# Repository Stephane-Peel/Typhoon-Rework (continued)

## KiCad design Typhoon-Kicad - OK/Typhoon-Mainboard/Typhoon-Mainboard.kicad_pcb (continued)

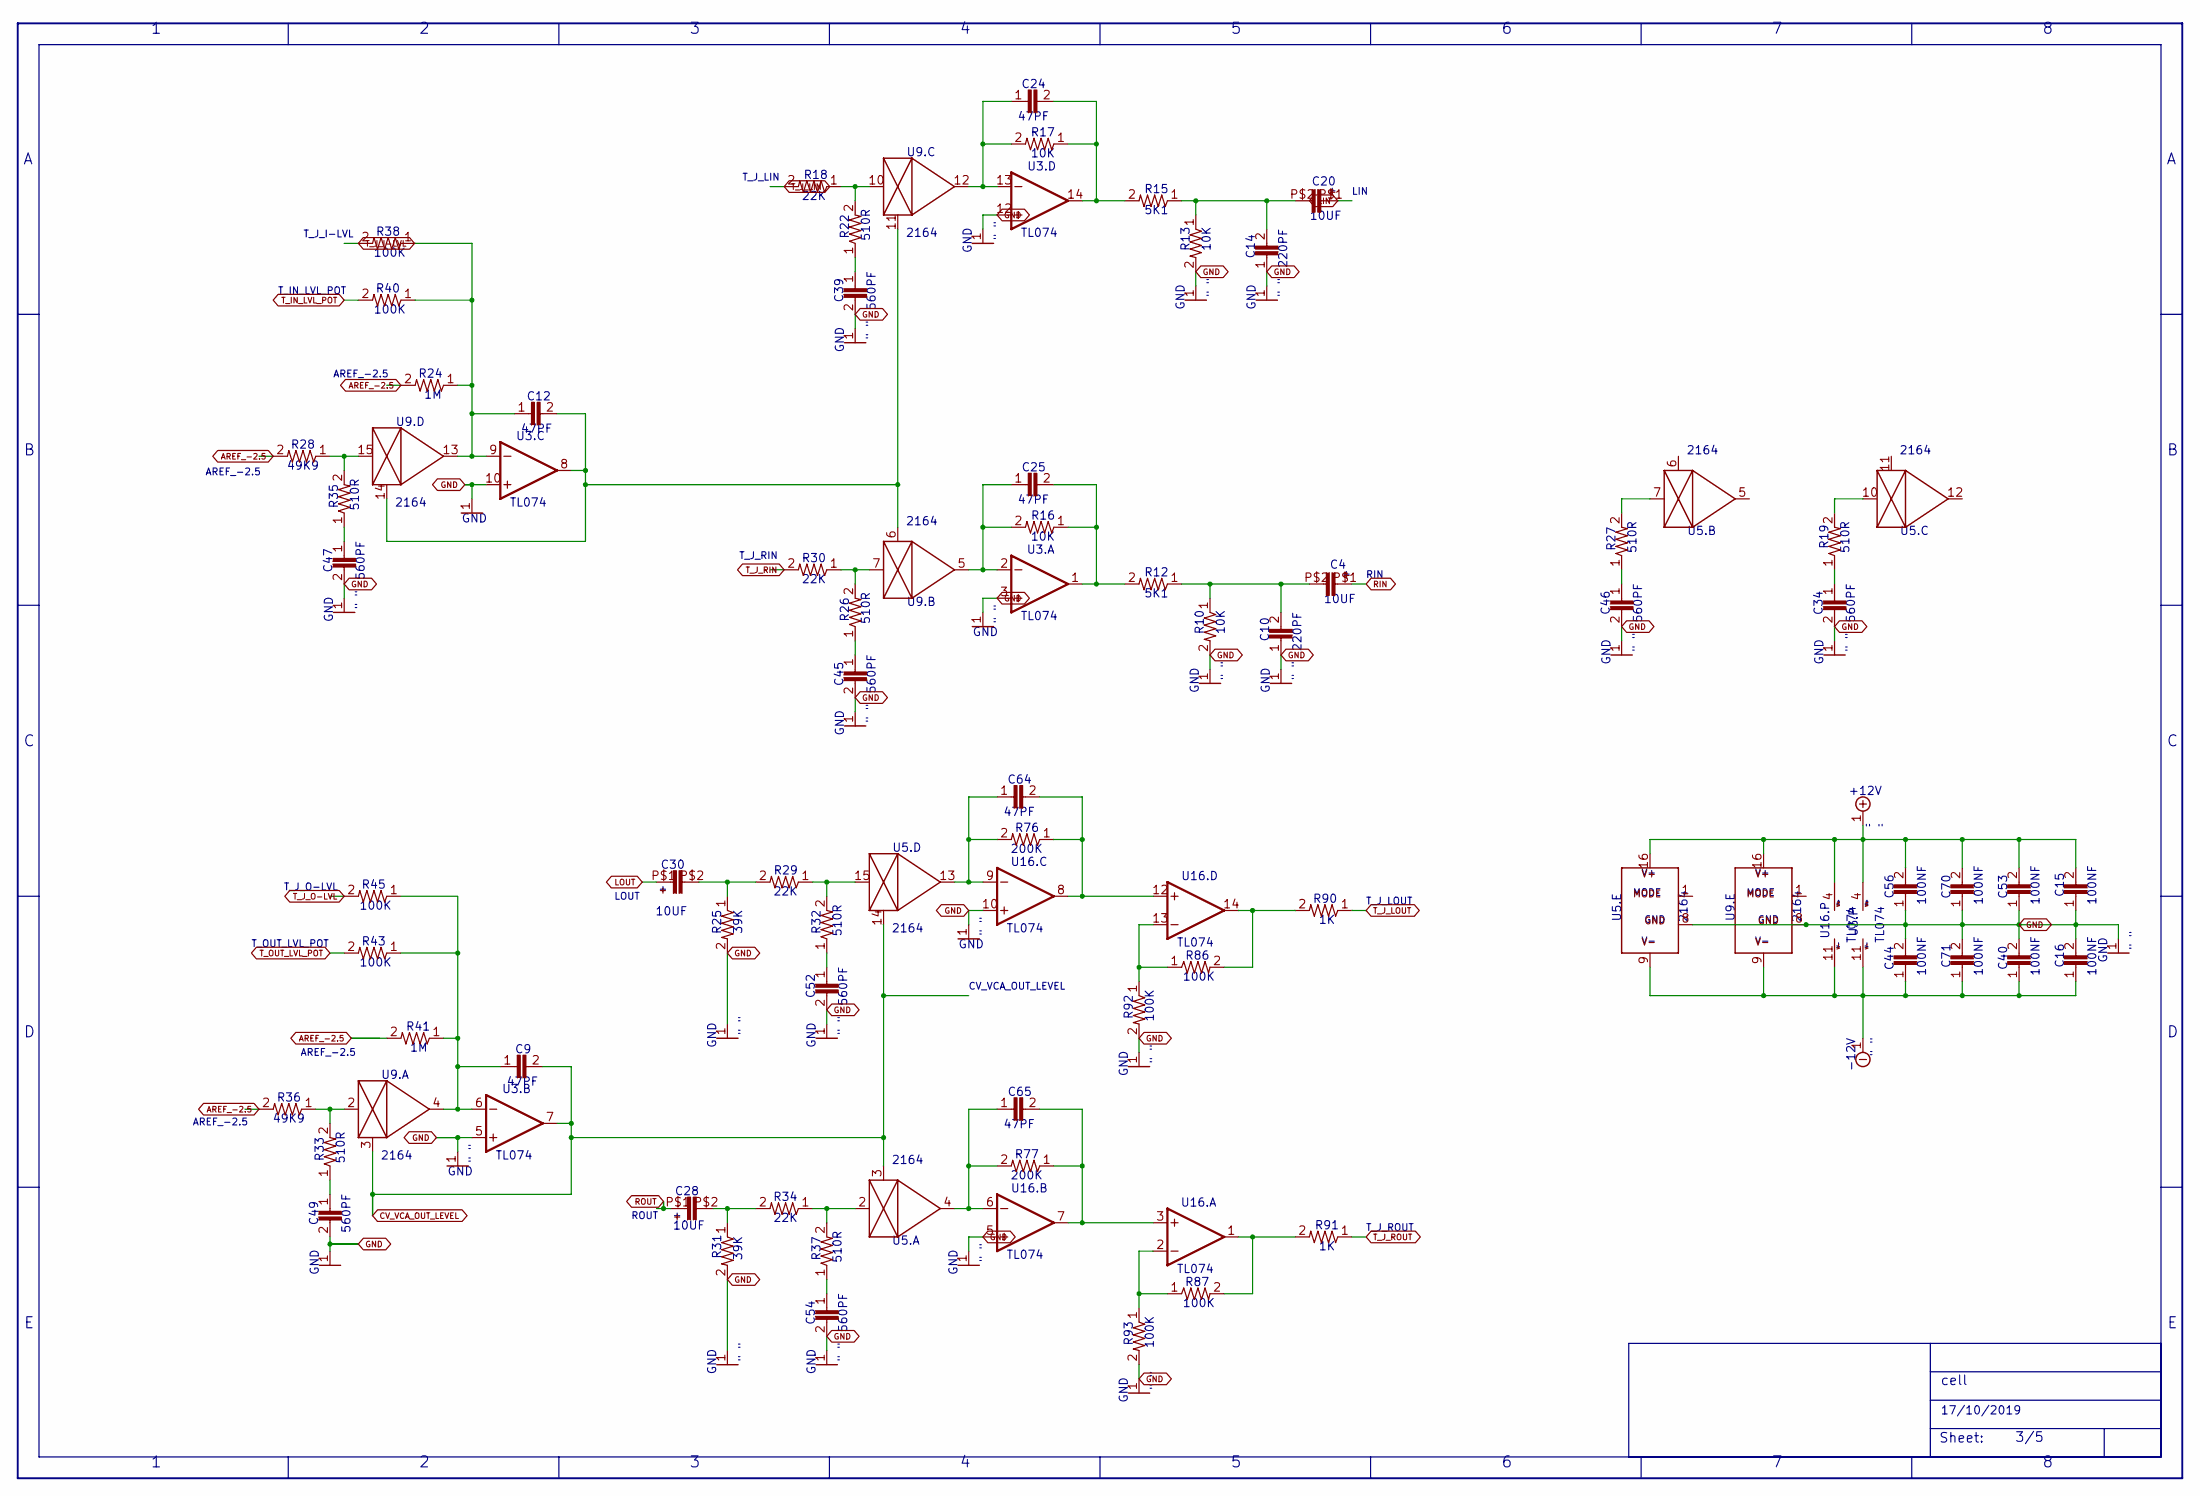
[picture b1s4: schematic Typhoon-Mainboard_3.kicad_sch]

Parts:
C4, C20, C28, C30: 10UF; EC-4X7
C9, C12, C24, C25, C64, C65: 47PF; CAP_0603
C10, C14: 220PF; CAP_0603
C15, C16, C40, C44, C53, C56, C70, C71: 100NF; CAP_0603
C34, C39, C45, C46, C47, C49, C52, C54: 560PF; CAP_0603
R10, R13, R16, R17: 10K; RES_0603
R12, R15: 5K1; RES_0603
R18, R29, R30, R34: 22K; RES_0603
R19, R22, R26, R27, R32, R33, R35, R37: 510R; RES_0603
R24, R41: 1M; RES_0603
R25, R31: 39K; RES_0603
R28, R36: 49K9; RES_0603
R38, R40, R43, R45, R86, R87, R92, R93: 100K; RES_0603
R76, R77: 200K; RES_0603
R90, R91: 1K; RES_0603
U3, U16: TL074; SO-14
U5, U9: 2164; SO-16

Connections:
+12V: C15.2, C53.2, C56.2, C70.2, U3.4 (V+), U5.16 (V+), U9.16 (V+), U16.4 (V+); also elsewhere on the board
-12V: C16.1, C40.1, C44.1, C71.1, U3.11 (V-), U5.9 (V-), U9.9 (V-), U16.11 (V-); also elsewhere on the board
AREF_-2.5: R24.2, R28.2, R36.2, R41.2; also elsewhere on the board
CV_VCA_OUT_LEVEL: C9.2, U3.7 (OUT), U5.3 (CTRL), U5.14 (CTRL), U9.3 (CTRL); also elsewhere on the board
LIN: C20.P$1 (POS); also elsewhere on the board
LOUT: C30.P$1 (POS); also elsewhere on the board
unnamed: C39.1, R22.1
unnamed: C45.1, R26.1
unnamed: C47.1, R35.1
unnamed: C12.2, U3.8 (OUT), U9.6 (CTRL), U9.11 (CTRL), U9.14 (CTRL)
unnamed: R26.2, R30.1, U9.7 (IN)
unnamed: R28.1, R35.2, U9.15 (IN)
unnamed: C25.1, R16.2, U3.2 (-IN), U9.5 (OUT)
unnamed: C25.2, R12.2, R16.1, U3.1 (OUT)
unnamed: C49.1, R33.1
unnamed: R33.2, R36.1, U9.2 (IN)
unnamed: C64.1, R76.2, U5.13 (OUT), U16.9 (-IN)
unnamed: C64.2, R76.1, U16.8 (OUT), U16.12 (+IN)
unnamed: R18.1, R22.2, U9.10 (IN)
unnamed: R27.2, U5.7 (IN)
unnamed: R29.1, R32.2, U5.15 (IN)
unnamed: C52.1, R32.1
unnamed: C30.P$2 (NEG), R25.1, R29.2
unnamed: C4.P$2 (NEG), C10.2, R10.1, R12.1
unnamed: C65.1, R77.2, U5.4 (OUT), U16.6 (-IN)
unnamed: C65.2, R77.1, U16.3 (+IN), U16.7 (OUT)
unnamed: R34.1, R37.2, U5.2 (IN)
unnamed: C54.1, R37.1
unnamed: C28.P$2 (NEG), R31.1, R34.2
unnamed: R19.2, U5.10 (IN)
unnamed: C24.1, R17.2, U3.13 (-IN), U9.12 (OUT)
unnamed: C24.2, R15.2, R17.1, U3.14 (OUT)
unnamed: R86.1, R92.1, U16.13 (-IN)
unnamed: C46.1, R27.1
unnamed: C34.1, R19.1
unnamed: R86.2, R90.2, U16.14 (OUT)
unnamed: R87.1, R93.1, U16.2 (-IN)
unnamed: R87.2, R91.2, U16.1 (OUT)
unnamed: C14.2, C20.P$2 (NEG), R13.1, R15.1
RIN: C4.P$1 (POS); also elsewhere on the board
ROUT: C28.P$1 (POS); also elsewhere on the board
T_IN_LVL_POT: R40.2; also elsewhere on the board
T_J_I-LVL: R38.2; also elsewhere on the board
T_J_LIN: R18.2; also elsewhere on the board
T_J_LOUT: R90.1; also elsewhere on the board
T_J_O-LVL: R45.2; also elsewhere on the board
T_J_RIN: R30.2; also elsewhere on the board
T_J_ROUT: R91.1; also elsewhere on the board
T_OUT_LVL_POT: R43.2; also elsewhere on the board
VCA_CTRL_INPUTS: C12.1, R24.1, R38.1, R40.1, U3.9 (-IN), U9.13 (OUT)
VCA_CTRL_INPUTS1: C9.1, R41.1, R43.1, R45.1, U3.6 (-IN), U9.4 (OUT)

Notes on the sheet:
TL074
C10
220PF
C64
R30
" "
R26
47PF
100NF
510R
C34
T_J_O-LVL
GND
22K
U9.D
560PF
C44
2164
R93
100K
T_J_ROUT
R24
10K
10UF
C70
U3.D
17/10/2019
R32
R91
C45
5K1
R90
RIN
MODE
R17
C53
U9.A
49K9
200K
C65

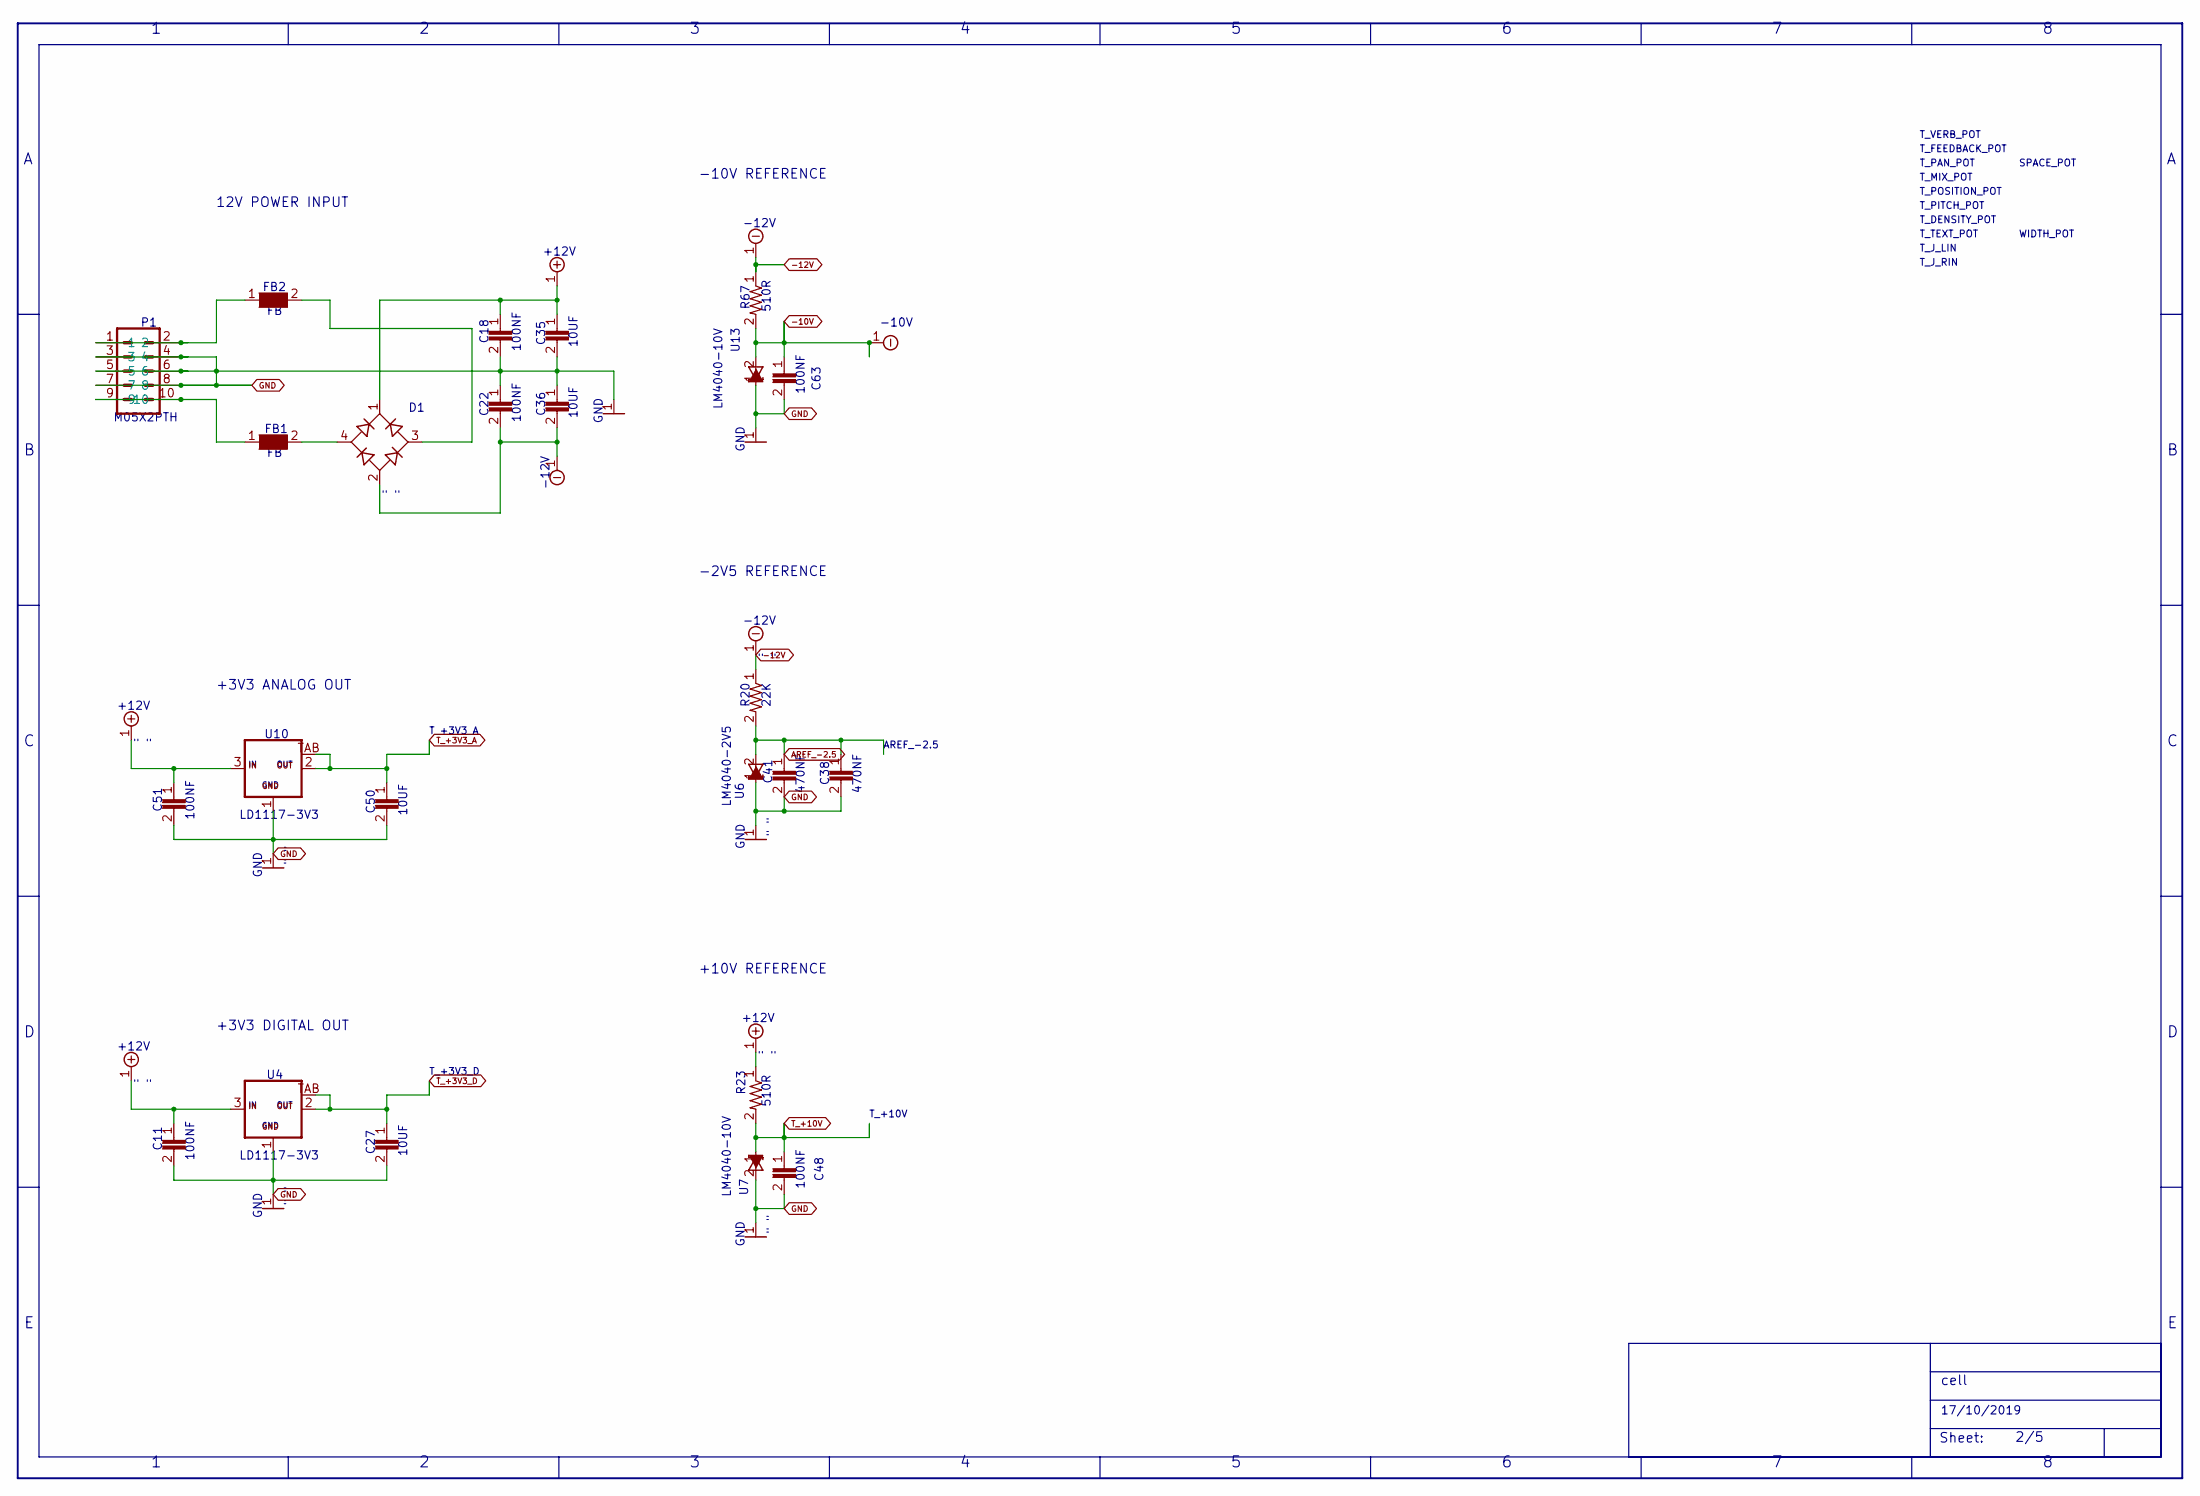
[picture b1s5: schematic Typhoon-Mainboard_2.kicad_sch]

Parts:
C11, C18, C22, C48, C51, C63: 100NF; CAP_0603
C27, C35, C36, C50: 10UF; C0805
C38, C41: 470NF; CAP_0603
D1: MB1S; SOP-4_6.5X2.54
FB1, FB2: FB; WUERTH-ELEKTRONIK_0603
P1: M05X2PTH; AVR_ICSP
R20: 22K; RES_0603
R23, R67: 510R; RES_0603
U4, U10: LD1117-3V3; SOT223
U6: LM4040-2V5; DBZ_R-PDSO-G3
U7, U13: LM4040-10V; DBZ_R-PDSO-G3

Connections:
+12V: C11.1, C18.1, C35.1, C51.1, D1.1 (+), R23.1, U4.3 (IN), U10.3 (IN); also elsewhere on the board
-10V: C63.1, R67.2, U13.2 (A); also elsewhere on the board
-12V: C22.2, C36.2, D1.2 (-), R20.1, R67.1; also elsewhere on the board
AREF_-2.5: C38.1, C41.1, R20.2, U6.2 (A); also elsewhere on the board
unnamed: FB2.1, P1.1, P1.2
unnamed: FB1.1, P1.9, P1.10
Net_38: D1.4 (AC1), FB1.2
Net_40: D1.3 (AC2), FB2.2
T_+3V3_A: C50.1, U10.2 (OUT), U10.TAB (OUT1); also elsewhere on the board
T_+10V: C48.1, R23.2, U7.1 (C); also elsewhere on the board

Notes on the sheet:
10UF
WIDTH_POT
T_J_RIN
SPACE_POT
-12V
C35
U13
+12V
C50
T_DENSITY_POT
+3V3 DIGITAL OUT
+10V REFERENCE
GND
T_+10V
cell
" "
M05X2PTH
100NF
LD1117-3V3
17/10/2019
12V POWER INPUT
C27
U10
R20
-10V REFERENCE
510R
T_J_LIN
C48
-10V
C22
T_PAN_POT
T_+3V3_D
FB1
C63
T_TEXT_POT
T_MIX_POT
Sheet:
LM4040-10V
C18
470NF

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
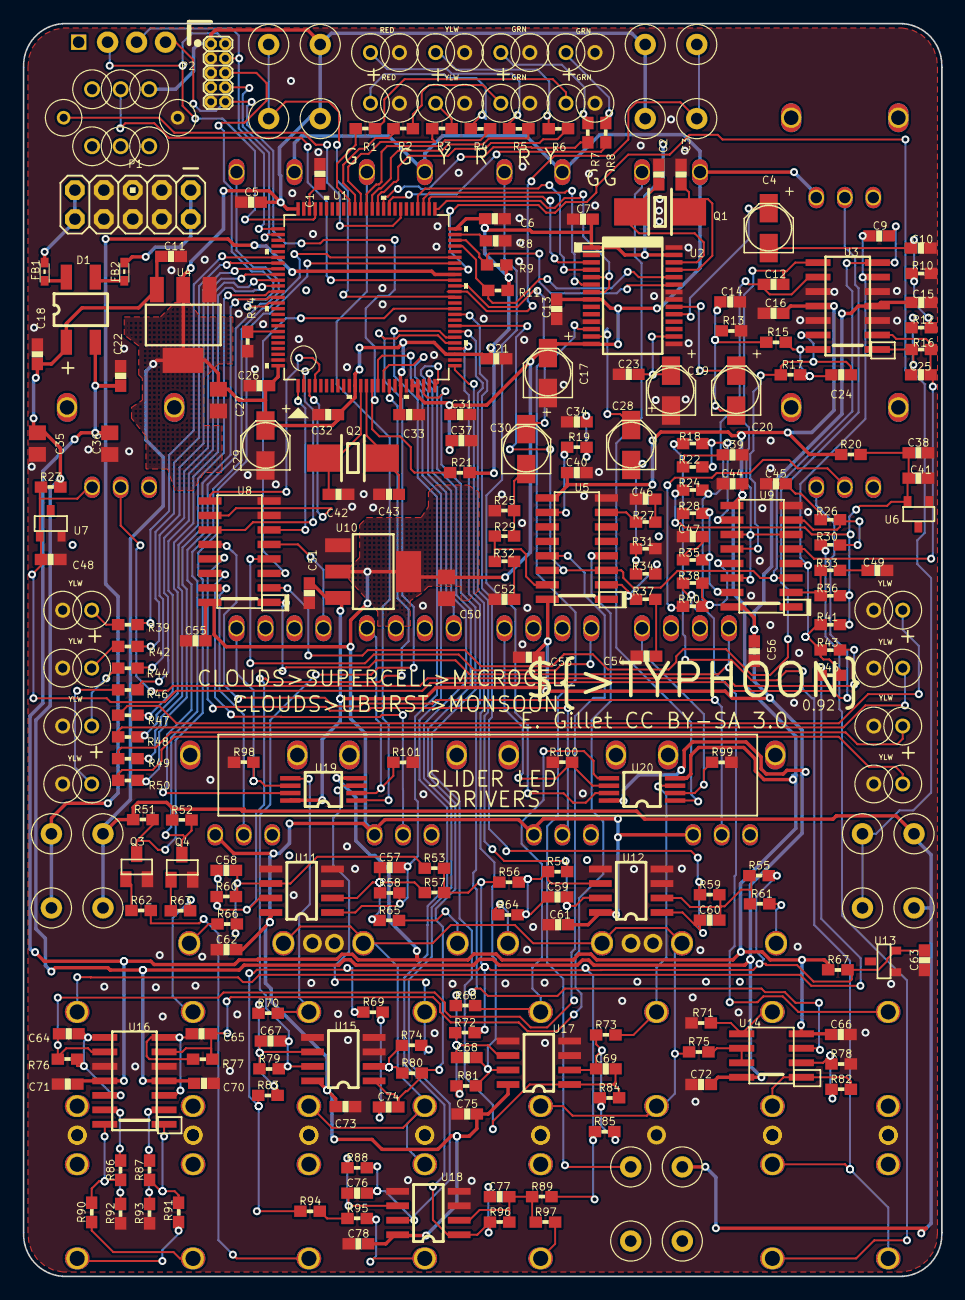
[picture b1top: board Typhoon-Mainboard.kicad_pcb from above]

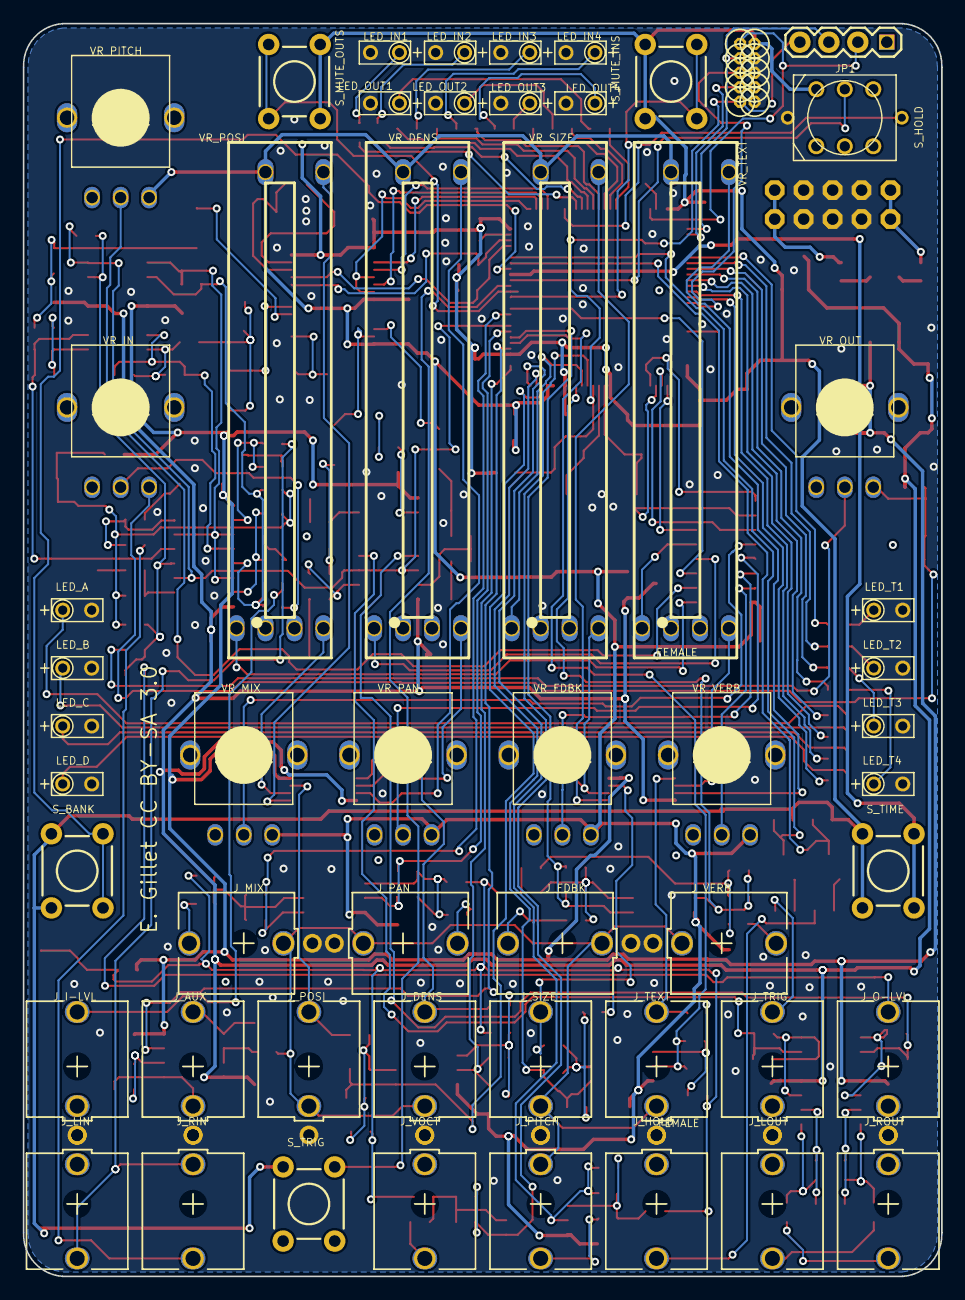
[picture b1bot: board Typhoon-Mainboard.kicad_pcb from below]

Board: 2 copper layers, 80.5 x 109.9 mm, 261 parts (53 on the bottom side), 182 nets.

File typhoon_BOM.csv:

Quantity,Value,Name,RefDes
2,2.2UF,C-EUC0603 (C-EU),"C1, C8"
4,18PF,C-EUC0603 (C-EU),"C2, C3, C42, C43"
7,10UF,C-EU-POL_4D (C-EU-POL),"C4, C17, C19, C20, C28, C29, C30"
33,100NF,C-EUC0603 (C-EU),"C5, C6, C7, C11, C13, C15, C16, C18, C21, C22, C23, C26, C31, C32, C33, C37, C40, C44, C48, C51, C53, C55, C56, C61, C62, C63, C66, C70, C71, C72, C73, C75, C78"
6,47PF,C-EUC0603 (C-EU),"C9, C12, C24, C25, C64, C65"
2,220PF,C-EUC0603 (C-EU),"C10, C14"
4,10UF,C-EUC0805 (C-EU),"C27, C35, C36, C50"
8,560PF,C-EUC0603 (C-EU),"C34, C39, C45, C46, C47, C49, C52, C54"
2,470NF,C-EUC0603 (C-EU),"C38, C41"
9,10NF,C-EUC0603 (C-EU),"C57, C58, C59, C60, C67, C68, C69, C74, C76"
1,1NF,C-EUC0603 (C-EU),C77
1,,MB1S,D1
2,FB,FERRITE_BEAD_0603 (FERRITE_BEAD),"FB1, FB2"
3,Eurorack Jack,EURO_JACKS_SMALL_SILK (EURO_JACK),"J_AUX, J_HOLD, J_TRIG"
16,Eurorack Jack,EURO_JACKS_SILK (EURO_JACK),"J_DENS, J_FDBK, J_I-LVL, J_LIN, J_LOUT, J_MIX, J_O-LVL, J_PAN, J_PITCH, J_POSI, J_RIN, J_ROUT, J_SIZE, J_TEXT, J_VERB, J_VOCT"
1,,M04PTH,JP1
10,2mm Yellow Diffused,LED_SILK (LED),"LED_A, LED_B, LED_C, LED_D, LED_IN3, LED_OUT3, LED_T1, LED_T2, LED_T3, LED_T4"
4,2mm Green Diffused,LED_SILK (LED),"LED_IN1, LED_IN2, LED_OUT1, LED_OUT2"
2,2mm Red Diffused,LED_SILK (LED),"LED_IN4, LED_OUT4"
1,M05X2PTH,M05X2PTH,P1
1,Mini JTAG Header,M05X2MINIJTAG (M05X2),P2
1,12.288MHz,TXC 7A crystal,Q1
1,8MHz,TXC 7A crystal,Q2
2,MMBT3904,-NPN-MMBT3904LT1SOT23-BEC (*-NPN-),"Q3, Q4"
5,100R,R-US_R0603 (R-US_),"R1, R2, R7, R8, R75"
18,1K,R-US_R0603 (R-US_),"R3, R4, R5, R6, R39, R42, R44, R46, R47, R48, R49, R50, R90, R91, R98, R99, R100, R101"
2,2K,R-US_R0603 (R-US_),"R9, R11"
6,10K,R-US_R0603 (R-US_),"R10, R13, R14, R16, R17, R21"
2,5K1,R-US_R0603 (R-US_),"R12, R15"
5,22K,R-US_R0603 (R-US_),"R18, R20, R29, R30, R34"
10,510R,R-US_R0603 (R-US_),"R19, R22, R23, R26, R27, R32, R33, R35, R37, R67"
3,1M,R-US_R0603 (R-US_),"R24, R41, R71"
2,39K,R-US_R0603 (R-US_),"R25, R31"
2,49K9,R-US_R0603 (R-US_),"R28, R36"
23,100K,R-US_R0603 (R-US_),"R38, R40, R43, R45, R51, R52, R61, R62, R63, R64, R65, R66, R68, R70, R73, R74, R82, R86, R87, R92, R93, R95, R97"
12,200K,R-US_R0603 (R-US_),"R53, R55, R56, R57, R69, R72, R76, R77, R78, R83, R85, R94"
9,33K,R-US_R0603 (R-US_),"R54, R58, R59, R60, R79, R80, R81, R84, R88"
1,180K,R-US_R0603 (R-US_),R89
1,47K,R-US_R0603 (R-US_),R96
5,Mini Button,TAC_SWITCHTACTILE_PTH_SILK (TAC_SWITCH),"S_BANK, S_MUTE_INS, S_MUTE_OUTS, S_TIME, S_TRIG"
1,LED Button White,LED_BUTTONLED_BUTTON_SILK (LED_BUTTON),S_HOLD
1,STM32F427VIT6,STM32F4XXV2,U1
1,,WM8731,U2
2,TL074,TL074_SO-14 (TL074),"U3, U16"
2,LD1117-3V3,LD1117-3V3 (LD1117),"U4, U10"
2,2164,SSI2164,"U5, U9"
1,LM4040-2V5,LM4041DBZA12 (LM4041),U6
2,LM4040-10V,LM4041DBZA12 (LM4041),"U7, U13"
1,4051,4051_MUX,U8
5,,MCP6002,"U11, U12, U15, U17, U18"
1,TL072,TL072_SO-8 (TL072),U14
2,,TLE2172,"U19, U20"
4,,bourns PTL LED slide pot ,"VR_DENS, VR_POSI, VR_SIZE, VR_TEXT"
7,P-10K-B,POT_9MM_SNAP-IN__ (POT_9MM_SNAP-IN_),"VR_FDBK, VR_IN, VR_MIX, VR_OUT, VR_PAN, VR_PITCH, VR_VERB"

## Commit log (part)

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2025-09-09 Update typhoon_BOM.csv
    Changed LEDs to 2mm
